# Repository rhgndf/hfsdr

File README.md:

# hfsdr

HFSDR: host software, firmware, and hardware design for the HFSDR USB device.

[Board PCB Files viewer](https://rhgndf.github.io/hfsdr/hardware)

## Getting started

Portable Mode (not connected to a PC)

1. Press the Rotary Encoder to 
    1. Enable/ Disable FM Audio Out mode (on disabled, it plays a constant tone)
    2. Cycle through different LED modes
<!--2. Turn the radio to change the FM Radio Frequency-->

Connected to a PC

1. Go to [the web ui](https://rhgndf.github.io/hfsdr/)
2. Connect & Pair a device
3. Set the frequency & gain
4. Pair the device again
5. Waterfall of the wireless world should start. If it doesn't look like [this](https://hackin7.github.io/lain-sdr-chall/assets/sample-C2LA0HHR.png), unplug the device and try again

- **User manual (slides):** [HFSDR User Manual](https://docs.google.com/presentation/d/1T5zb-2KSN37Saw5E9nwcajVOSR3CzVYfAOpIypQLBcQ/edit?usp=sharing)
- **Lain Themed Web UI** [lain-sdr-ui](https://hackin7.github.io/lain-sdr-chall)
- **Host testing (Python probe, GNU Radio `.grc` examples, drivers, protocol):** [docs/host-guide.md](docs/host-guide.md)

## Troubleshooting

- **No firmware:** Enter the bootloader by holding down BOOT and pressing the RST button. Use `wchisp` to flash the elf file in the releases
- **USB / stream flaky:** Unplug the board or reset it a few times. The host stack sometimes needs a power cycle before enumeration, WinUSB binding, or streaming stabilizes.
- **Using with GNURadio/ Python Scripting:** See the driver and probe sections in [docs/host-guide.md](docs/host-guide.md).
- **Reset:** Do not hold the reset button for too long 

## Repository layout

| Path | Contents |
|------|----------|
| `ch32v305/` | Firmware (CH32V305). Build, flash, toolchain: [ch32v305/README.md](ch32v305/README.md). |
| `client-sw/` | Host Python (`hfsdr_probe`, PyUSB helpers), GNU Radio blocks and examples (`gr-hfsdr-lib`, `.grc`). |
| `docs/` | [host-guide.md](docs/host-guide.md) — primary host-side documentation. |
| `hardware/` | KiCad project and related hardware files. |
| `scripts/` | Helper scripts (e.g. udev `99-hfsdr.rules`, Windows USB checks). |
| `ui/` | WebUSB Web UI (Svelte/Vite). Deployed build: `homepage` in [ui/package.json](ui/package.json). |

## Credits

1. rhgndf - hard carry schematic & everything inside actually
2. Hackin7 - Art, PCB rough layout & routing & some embedded
3. Hack & Roll Cursor Credits + Codex - allow us to do this while being overseas/ having full time jobs
4. https://github.com/ttrftech/CentSDR - Useful reference

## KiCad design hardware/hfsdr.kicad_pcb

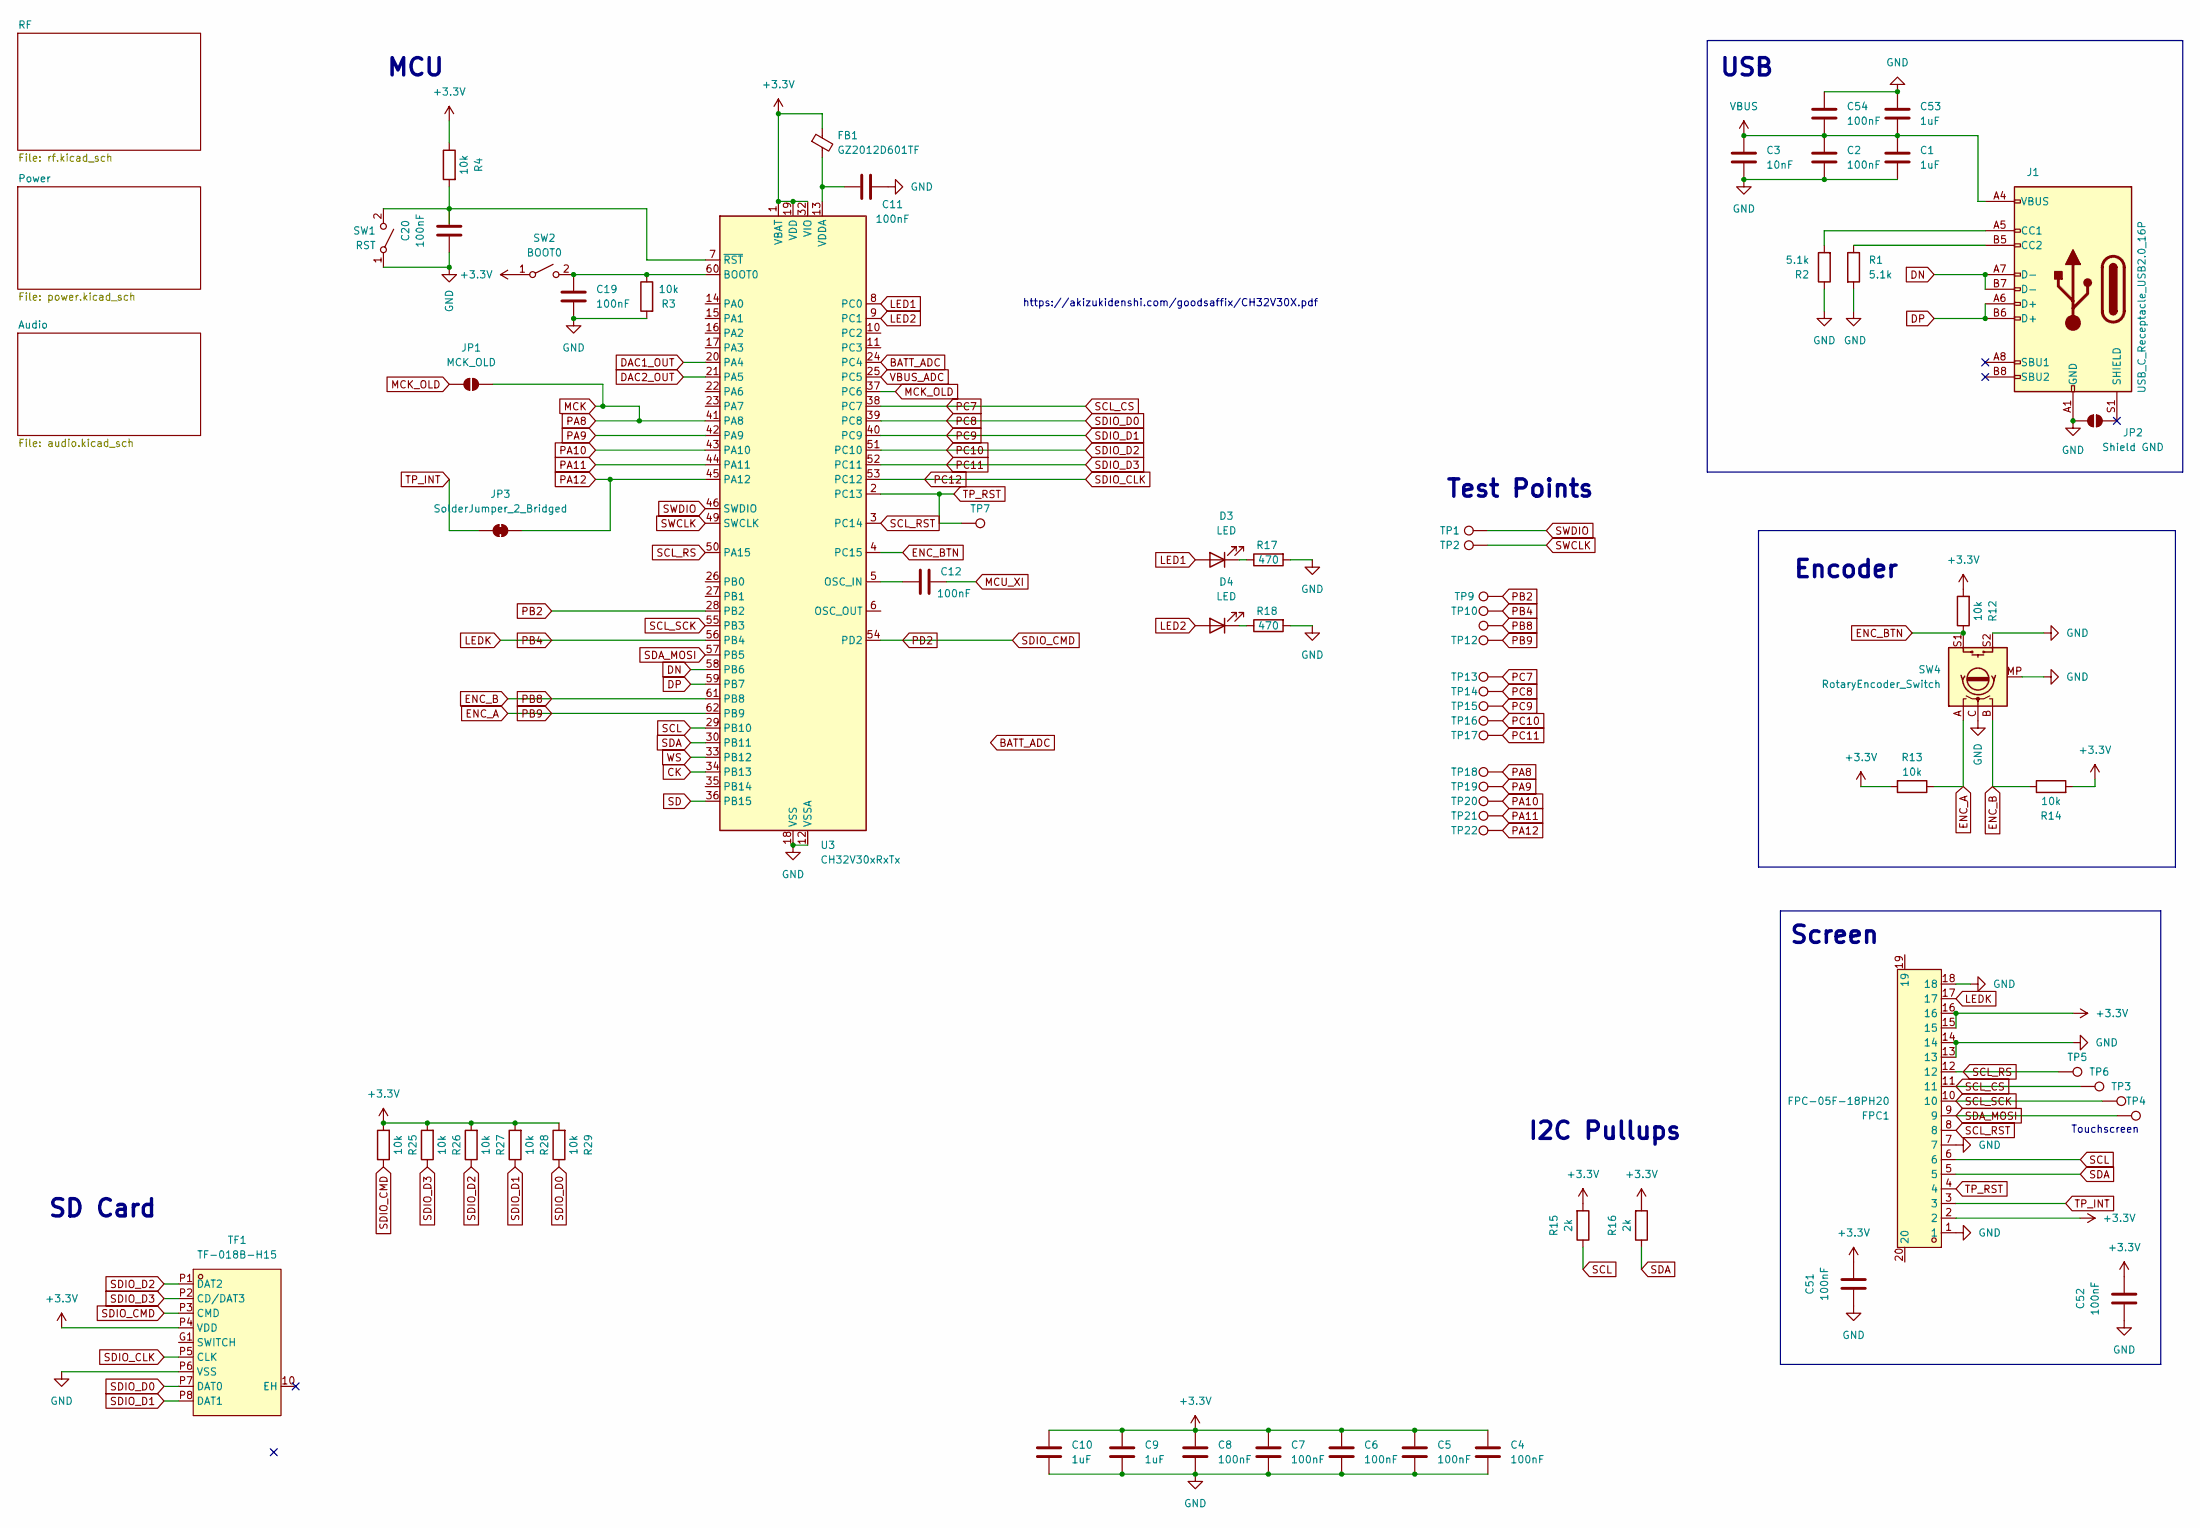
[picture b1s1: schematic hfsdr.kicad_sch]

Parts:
C1, C9, C10, C53: 1uF; C_0805_2012Metric_Pad1.18x1.45mm_HandSolder
C2, C4, C5, C6, C7, C8, C11, C12, C19, C20, C51, C52, C54: 100nF; C_0805_2012Metric_Pad1.18x1.45mm_HandSolder
C3: 10nF; C_0805_2012Metric_Pad1.18x1.45mm_HandSolder
D3, D4: LED; LED1206-RD_RED_XL-3216SURC-FB
FB1: GZ2012D601TF; L_0805_2012Metric_Pad1.05x1.20mm_HandSolder
FPC1: FPC-05F-18PH20; FPC-SMD_18P-P0.50_FPC-05F-18PH20; LCSC Part C2856802
J1: USB_C_Receptacle_USB2.0_16P; USB_C_Receptacle_GCT_USB4105-xx-A_16P_TopMnt_Horizontal
JP1: MCK_OLD; SolderJumper-2_P1.3mm_Open_RoundedPad1.0x1.5mm
JP2: Shield GND; SolderJumper-2_P1.3mm_Open_RoundedPad1.0x1.5mm
JP3: SolderJumper_2_Bridged; SolderJumper-2_P1.3mm_Bridged2Bar_RoundedPad1.0x1.5mm
R1, R2: 5.1k; R_0805_2012Metric_Pad1.20x1.40mm_HandSolder
R3, R4, R12, R13, R14, R25, R26, R27, R28, R29: 10k; R_0805_2012Metric_Pad1.20x1.40mm_HandSolder
R15, R16: 2k; R_0805_2012Metric_Pad1.20x1.40mm_HandSolder
R17, R18: 470; R_0805_2012Metric
SW1: RST; SW_Push_1P1T_XKB_TS-1187A
SW2: BOOT0; SW_Push_1P1T_XKB_TS-1187A
SW4: RotaryEncoder_Switch; RotaryEncoder_Alps_EC11E-Switch_Vertical_H20mm_MountingHoles
TF1: TF-018B-H15; TF-SMD_TF-018B-H15; LCSC Part C2962372
TP1, TP2, TP3, TP4, TP5, TP6, TP7, TP9, TP10, TP11, TP12, TP13, TP14, TP15, TP16, TP17, TP18, TP19, TP20, TP21, TP22: TestPoint; TestPoint_Pad_1.0x1.0mm
U3: CH32V30xRxTx; LQFP-64_10x10mm_P0.5mm

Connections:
+3.3V: C4.1, C5.1, C6.1, C7.1, C8.1, C9.1, C10.1, C51.2, C52.2, FB1.1, FPC1.2, FPC1.15, FPC1.16, R4.1, R12.2, R13.2, R14.2, R15.2, R16.2, R25.2, R26.2, R27.2, R28.2, R29.2, SW2.1 (A), TF1.P4 (VDD), U3.1 (VBAT), U3.19 (VDD), U3.32 (VIO), U3.48 (VDD), U3.64 (VIO); also elsewhere on the board
BATT_ADC: U3.24 (PC4); also elsewhere on the board
CK: U3.34 (PB13); also elsewhere on the board
DAC1_OUT: U3.20 (PA4); also elsewhere on the board
DAC2_OUT: U3.21 (PA5); also elsewhere on the board
DN: J1.A7 (D-), J1.B7 (D-), U3.58 (PB6)
DP: J1.A6 (D+), J1.B6 (D+), U3.59 (PB7)
ENC_A: R13.1, SW4.A, TP12.1 (1_1), U3.62 (PB9)
ENC_B: R14.1, SW4.B, TP11.1 (1_1), U3.61 (PB8)
ENC_BTN: R12.1, SW4.S1, U3.4 (PC15)
GND: C1.2, C2.2, C3.2, C4.2, C5.2, C6.2, C7.2, C8.2, C9.2, C10.2, C11.2, C19.2, C20.1, C51.1, C52.1, C53.1, C54.1, FPC1.1, FPC1.7, FPC1.13, FPC1.14, FPC1.18, J1.A1 (GND), J1.A12 (GND), J1.B1 (GND), J1.B12 (GND), JP2.1 (A_1), R1.2, R2.1, R3.2, R17.2, R18.2, SW1.1 (A), SW4.C, SW4.MP, SW4.S2, TF1.P6 (VSS), U3.12 (VSSA), U3.18 (VSS), U3.31 (VSS), U3.47 (VSS), U3.63 (VSS); also elsewhere on the board
LED1: D3.2 (A), U3.8 (PC0)
LED2: D4.2 (A), U3.9 (PC1)
LEDK: FPC1.17, TP10.1 (1_1), U3.56 (PB4)
MCK: JP1.2 (B), TP18.1 (1_1), U3.41 (PA8); also elsewhere on the board
MCK_OLD: JP1.1 (A), U3.37 (PC6)
MCU_XI: C12.2; also elsewhere on the board
unnamed: D3.1 (K), R17.1
unnamed: D4.1 (K), R18.1
unnamed: J1.A5 (CC1), R2.2
unnamed: J1.B5 (CC2), R1.1
unnamed: C20.2, R4.2, SW1.2 (B), U3.7 (~RST)
unnamed: C19.1, R3.1, SW2.2 (B), U3.60 (BOOT0)
unnamed: C12.1, U3.5 (OSC_IN)
unnamed: C11.1, FB1.2, U3.13 (VDDA)
PA9: TP19.1 (1_1), U3.42 (PA9)
PA10: TP20.1 (1_1), U3.43 (PA10)
PA11: TP21.1 (1_1), U3.44 (PA11); also elsewhere on the board
PA12: JP3.2 (B), TP22.1 (1_1), U3.45 (PA12)
PB2: TP9.1 (1_1), U3.28 (PB2)
PC7: FPC1.11, TP6.1 (1_1), TP13.1 (1_1), U3.38 (PC7)
PC8: R29.1, TF1.P7 (DAT0), TP14.1 (1_1), U3.39 (PC8)
PC9: R28.1, TF1.P8 (DAT1), TP15.1 (1_1), U3.40 (PC9)
PC10: R27.1, TF1.P1 (DAT2), TP16.1 (1_1), U3.51 (PC10)
PC11: R26.1, TF1.P2 (CD/DAT3), TP17.1 (1_1), U3.52 (PC11)
PC12: TF1.P5 (CLK), U3.53 (PC12)
PD2: R25.1, TF1.P3 (CMD), U3.54 (PD2)
SCL: FPC1.6, R15.1, U3.29 (PB10); also elsewhere on the board
SCL_RS: FPC1.12, TP5.1 (1_1), U3.50 (PA15)
SCL_RST: FPC1.8, U3.3 (PC14)
SCL_SCK: FPC1.10, TP3.1 (1_1), U3.55 (PB3)
SD: U3.36 (PB15); also elsewhere on the board
SDA: FPC1.5, R16.1, U3.30 (PB11); also elsewhere on the board
SDA_MOSI: FPC1.9, TP4.1 (1_1), U3.57 (PB5)
SWCLK: TP2.1 (1_1), U3.49 (SWCLK)
SWDIO: TP1.1 (1_1), U3.46 (SWDIO)
TP_INT: FPC1.3, JP3.1 (A)
TP_RST: FPC1.4, TP7.1 (1_1), U3.2 (PC13)
VBUS: C1.1, C2.1, C3.1, C53.2, C54.2, J1.A4 (VBUS), J1.A9 (VBUS), J1.B4 (VBUS), J1.B9 (VBUS); also elsewhere on the board
VBUS_ADC: U3.25 (PC5); also elsewhere on the board
WS: U3.33 (PB12); also elsewhere on the board

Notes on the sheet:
USB
SD Card
https://akizukidenshi.com/goodsaffix/CH32V30X.pdf
Encoder
Touchscreen
Screen
MCU
Test Points
I2C Pullups

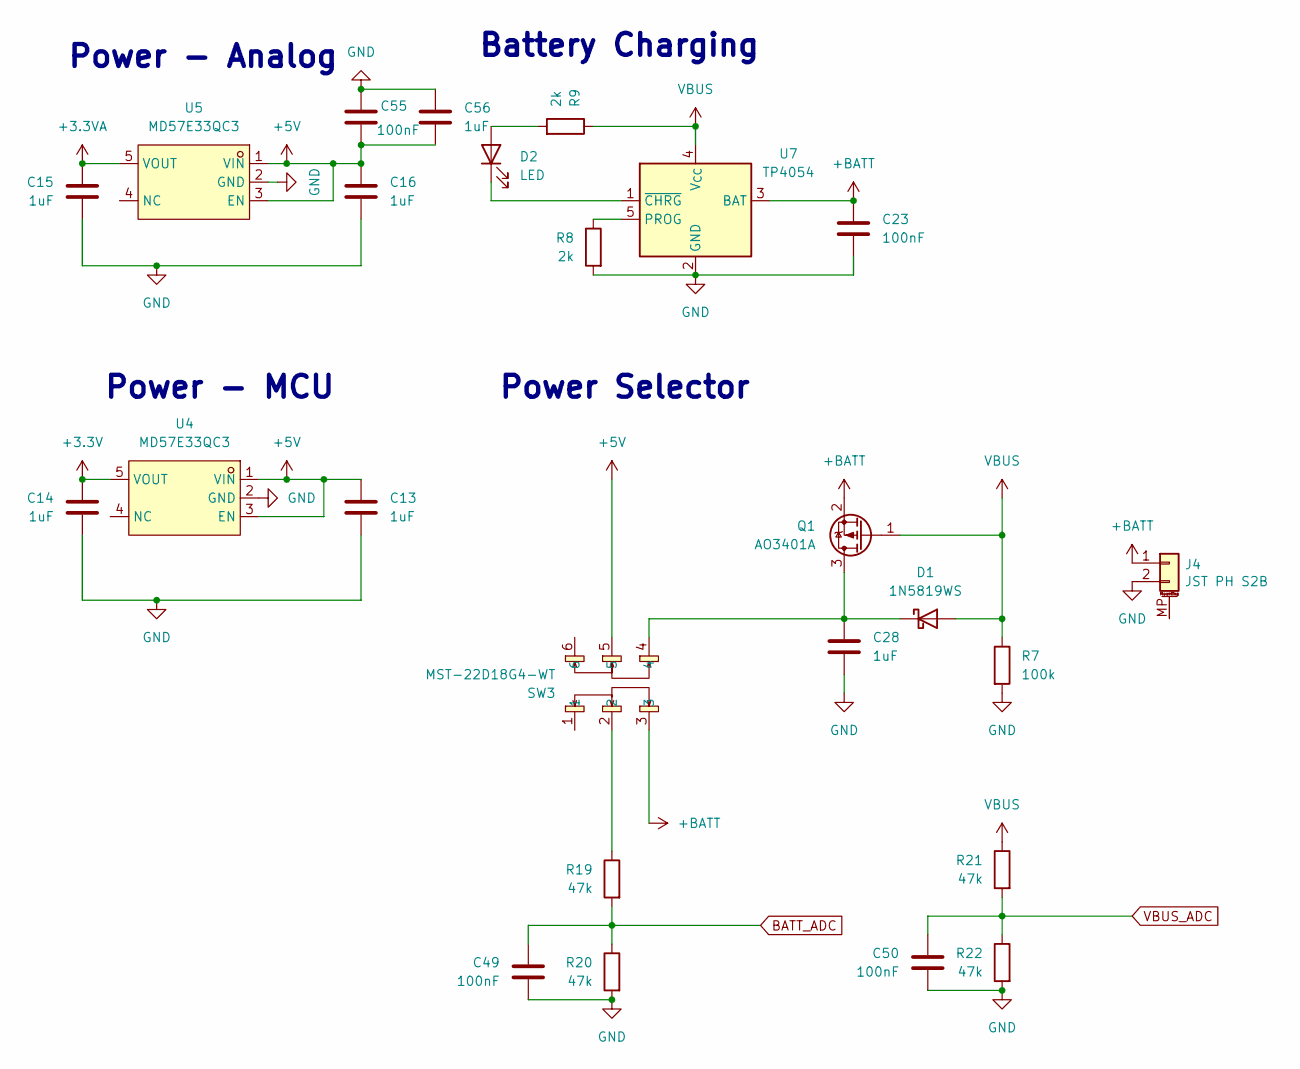
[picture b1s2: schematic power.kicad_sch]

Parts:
C13, C14, C15, C16, C28, C56: 1uF; C_0805_2012Metric_Pad1.18x1.45mm_HandSolder
C23, C49, C50, C55: 100nF; C_0805_2012Metric_Pad1.18x1.45mm_HandSolder
D1: 1N5819WS; D_SOD-323
D2: LED; LED_0805_2012Metric
J4: JST PH S2B; JST_PH_S2B-PH-SM4-TB_1x02-1MP_P2.00mm_Horizontal; LCSC C505023
Q1: AO3401A; SOT-23
R7: 100k; R_0805_2012Metric_Pad1.20x1.40mm_HandSolder
R8, R9: 2k; R_0805_2012Metric_Pad1.20x1.40mm_HandSolder
R19, R20, R21, R22: 47k; R_0805_2012Metric_Pad1.20x1.40mm_HandSolder
SW3: MST-22D18G4-WT; SW-SMD_MST-22D18G4-WT; LCSC Part C7507448
U4, U5: MD57E33QC3; SOT-23-5_L3.0-W1.7-P0.95-LS2.8-BR; LCSC Part C920562
U7: TP4054; TSOT-23-5

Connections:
+3.3V: C14.1, U4.5 (VOUT); also elsewhere on the board
+3.3VA: C15.1, U5.5 (VOUT); also elsewhere on the board
+5V: C13.1, C16.1, C55.2, C56.2, SW3.5, U4.1 (VIN), U4.3 (EN), U5.1 (VIN), U5.3 (EN)
+BATT: C23.1, J4.1, Q1.2 (S), SW3.3, U7.3 (BAT)
BATT_ADC: C49.1, R19.2, R20.1; also elsewhere on the board
GND: C13.2, C14.2, C15.2, C16.2, C23.2, C28.2, C49.2, C50.2, C55.1, C56.1, J4.2, R7.2, R8.2, R20.2, R22.2, U4.2 (GND), U5.2 (GND), U7.2 (GND); also elsewhere on the board
unnamed: C28.1, D1.1 (K), Q1.3 (D), SW3.4
unnamed: D2.2 (A), R9.2
unnamed: D2.1 (K), U7.1 (~CHRG)
unnamed: R19.1, SW3.2
unnamed: R8.1, U7.5 (PROG)
VBUS: D1.2 (A), Q1.1 (G), R7.1, R9.1, R21.1, U7.4 (V_{CC}); also elsewhere on the board
VBUS_ADC: C50.1, R21.2, R22.1; also elsewhere on the board

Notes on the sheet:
Power - Analog
Battery Charging
Power - MCU
Power Selector

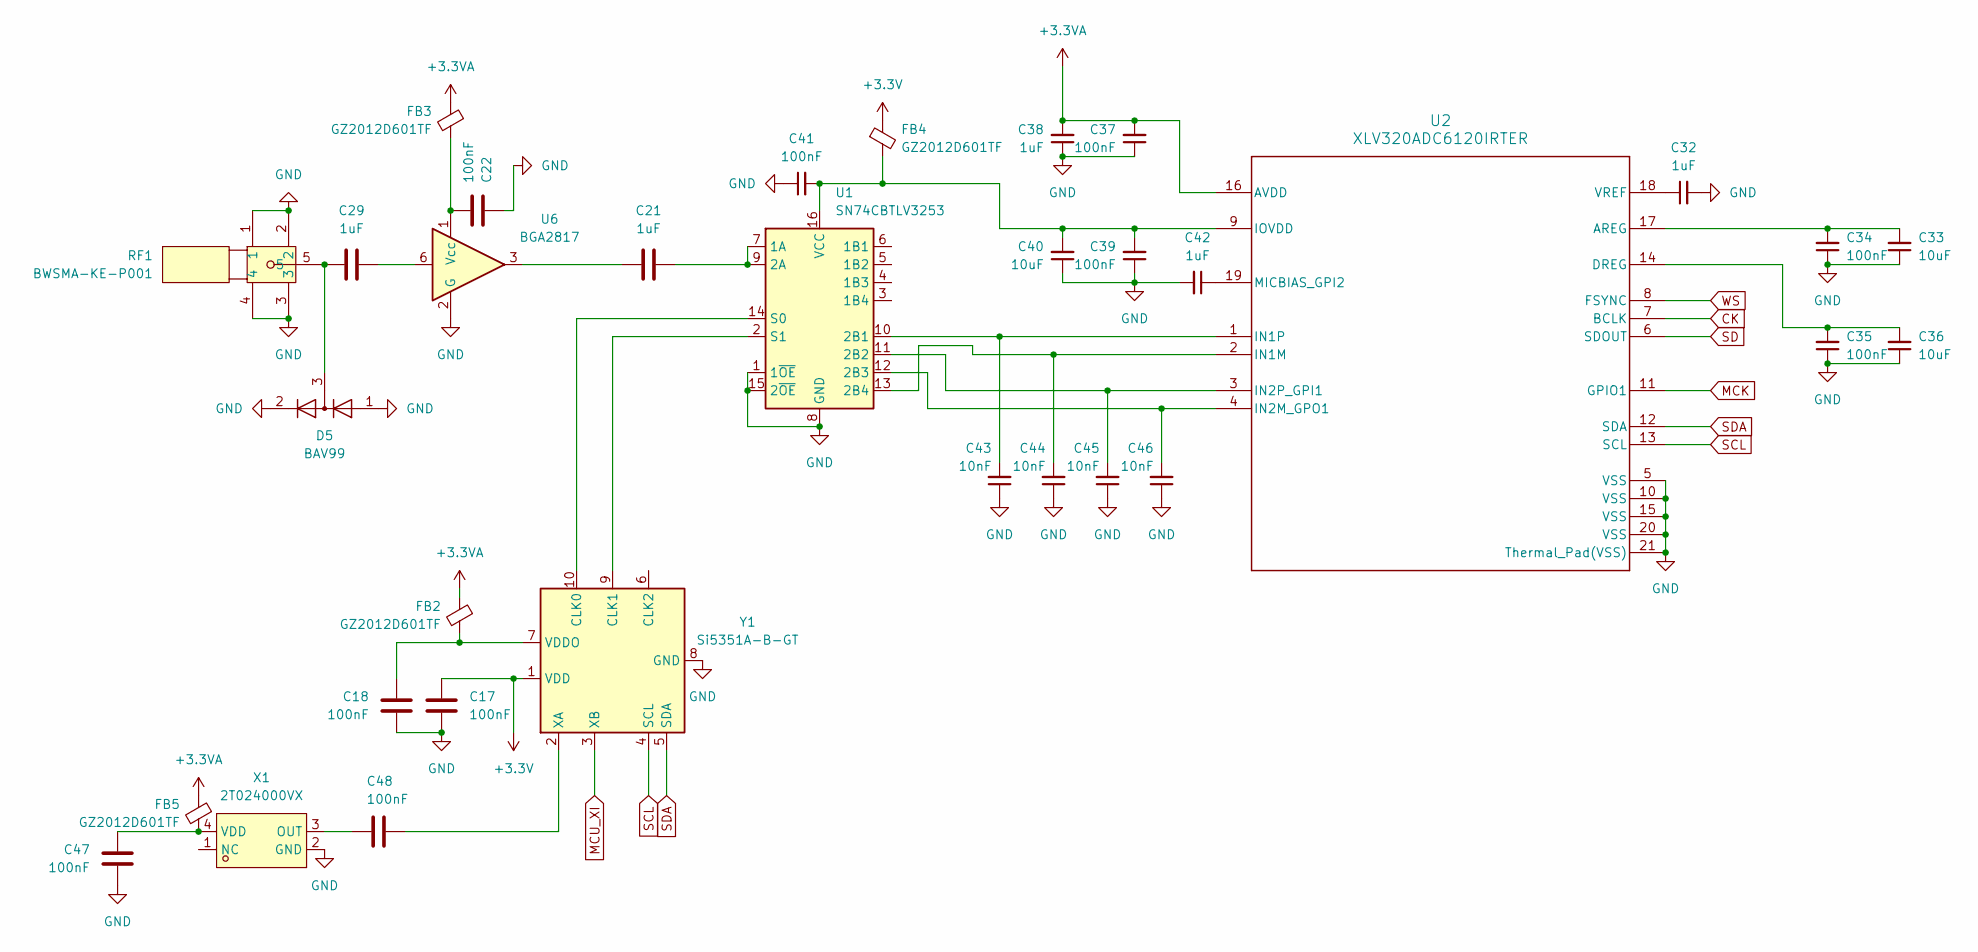
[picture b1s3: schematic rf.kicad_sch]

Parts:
C17, C18, C22, C34, C35, C37, C39, C41, C47, C48: 100nF; C_0805_2012Metric_Pad1.18x1.45mm_HandSolder
C21, C29, C32, C38, C42: 1uF; C_0805_2012Metric_Pad1.18x1.45mm_HandSolder
C33, C36, C40: 10uF; C_0805_2012Metric_Pad1.18x1.45mm_HandSolder
C43, C44, C45, C46: 10nF; C_0805_2012Metric_Pad1.18x1.45mm_HandSolder
D5: BAV99; SOT-23
FB2, FB3, FB4, FB5: GZ2012D601TF; L_0805_2012Metric_Pad1.05x1.20mm_HandSolder
RF1: BWSMA-KE-P001; SMA-SMD_BWSMA-KE-P001; LCSC Part C496550
U1: SN74CBTLV3253; SOIC-16_3.9x9.9mm_P1.27mm
U2: XLV320ADC6120IRTER; RTE0020A-MFG
U6: BGA2817; SOT-363_SC-70-6
X1: 2T024000VX; OSC-SMD_4P-L2.5-W2.0-BL_X1G0054210307; LCSC Part C47018486
Y1: Si5351A-B-GT; MSOP-10_3x3mm_P0.5mm

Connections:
+3.3V: C17.2, FB4.1, Y1.1 (VDD); also elsewhere on the board
+3.3VA: C37.2, C38.2, FB2.1, FB3.1, FB5.1, U2.16 (AVDD); also elsewhere on the board
CK: U2.7 (BCLK); also elsewhere on the board
GND: C17.1, C18.2, C22.1, C32.2, C33.1, C34.1, C35.1, C36.1, C37.1, C38.1, C39.1, C40.1, C41.1, C42.2, C43.1, C44.1, C45.1, C46.1, C47.2, D5.1 (K), D5.2 (A), RF1.1, RF1.2, RF1.3, RF1.4, U1.1 (1~OE), U1.8 (GND), U1.15 (2~OE), U2.5 (VSS), U2.10 (VSS), U2.15 (VSS), U2.20 (VSS), U2.21 (Thermal_Pad(VSS)), U6.2 (G), U6.4 (G), U6.5 (G), X1.2 (GND), Y1.8 (GND); also elsewhere on the board
MCK: U2.11 (GPIO1); also elsewhere on the board
MCU_XI: Y1.3 (XB); also elsewhere on the board
unnamed: C21.2, U6.3
unnamed: C29.1, U6.6
unnamed: C29.2, D5.3 (K), RF1.5
unnamed: C21.1, U1.7 (1A), U1.9 (2A)
unnamed: C43.2, U1.10 (2B1), U2.1 (IN1P)
unnamed: C45.2, U1.11 (2B2), U2.3 (IN2P_GPI1)
unnamed: C46.2, U1.12 (2B3), U2.4 (IN2M_GPO1)
unnamed: C44.2, U1.13 (2B4), U2.2 (IN1M)
unnamed: U1.14 (S0), Y1.10 (CLK0)
unnamed: U1.2 (S1), Y1.9 (CLK1)
unnamed: C39.2, C40.2, C41.2, FB4.2, U1.16 (VCC), U2.9 (IOVDD)
unnamed: C33.2, C34.2, U2.17 (AREG)
unnamed: C35.2, C36.2, U2.14 (DREG)
unnamed: C42.1, U2.19 (MICBIAS_GPI2)
unnamed: C32.1, U2.18 (VREF)
unnamed: C22.2, FB3.2, U6.1 (Vcc)
unnamed: C48.2, X1.3 (OUT)
unnamed: C47.1, FB5.2, X1.4 (VDD)
unnamed: C18.1, FB2.2, Y1.7 (VDDO)
unnamed: C48.1, Y1.2 (XA)
SCL: U2.13 (SCL), Y1.4 (SCL); also elsewhere on the board
SD: U2.6 (SDOUT); also elsewhere on the board
SDA: U2.12 (SDA), Y1.5 (SDA); also elsewhere on the board
WS: U2.8 (FSYNC); also elsewhere on the board

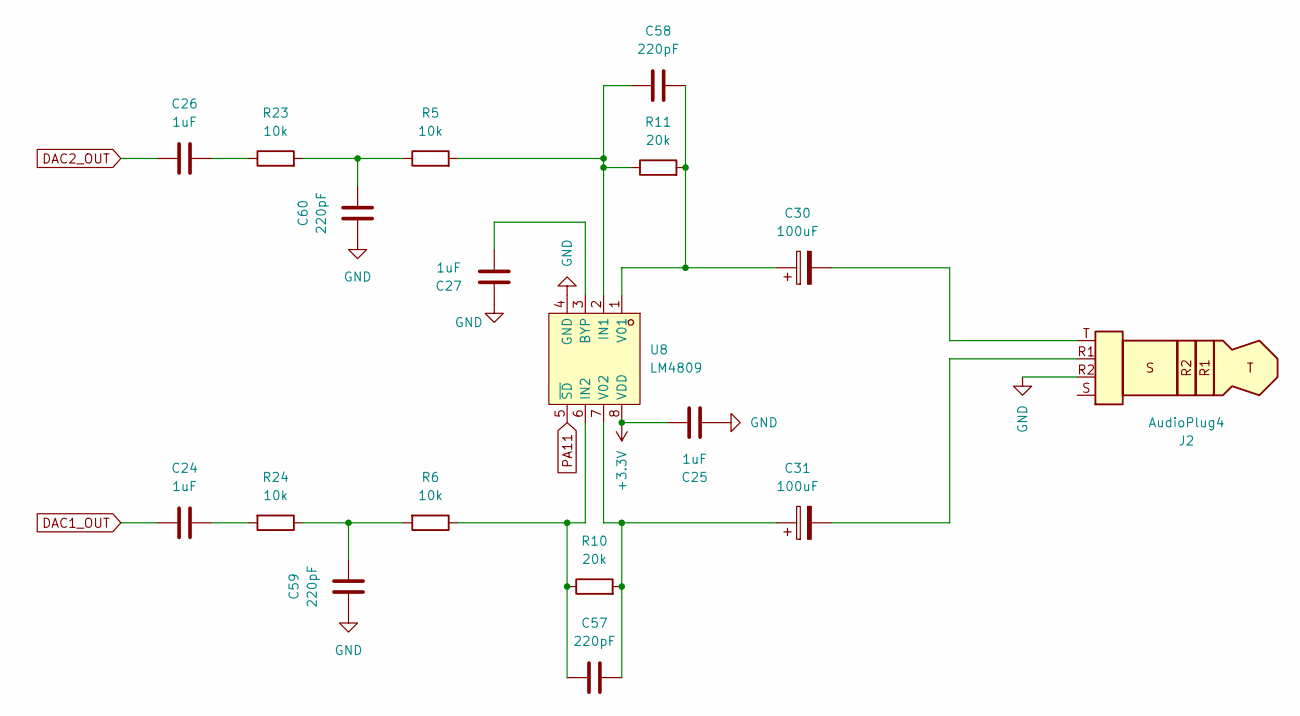
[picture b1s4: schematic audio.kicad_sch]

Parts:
C24, C25, C26, C27: 1uF; C_0805_2012Metric_Pad1.18x1.45mm_HandSolder
C30, C31: 100uF; CP_EIA-3528-15_AVX-H_HandSolder
C57, C58, C59, C60: 220pF; C_0805_2012Metric_Pad1.18x1.45mm_HandSolder
J2: AudioPlug4; Jack_3.5mm_KoreanHropartsElec_PJ-320D-4A_Horizontal
R5, R6, R23, R24: 10k; R_0805_2012Metric_Pad1.20x1.40mm_HandSolder
R10, R11: 20k; R_0805_2012Metric_Pad1.20x1.40mm_HandSolder
U8: LM4809; MSOP-8_L3.0-W3.0-P0.65-LS4.9-BL; LCSC Part C5125075

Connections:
+3.3V: C25.2, U8.8 (VDD); also elsewhere on the board
DAC1_OUT: C24.2; also elsewhere on the board
DAC2_OUT: C26.2; also elsewhere on the board
GND: C25.1, C27.2, C59.2, C60.2, J2.R2, U8.4 (GND); also elsewhere on the board
unnamed: C24.1, R24.2
unnamed: C26.1, R23.1
unnamed: C30.2, J2.T
unnamed: C31.2, J2.R1
unnamed: C59.1, R6.2, R24.1
unnamed: C60.1, R5.1, R23.2
unnamed: C27.1, U8.3 (BYP)
unnamed: C58.2, R5.2, R11.1, U8.2 (IN1)
unnamed: C57.2, R6.1, R10.1, U8.6 (IN2)
unnamed: C30.1, C58.1, R11.2, U8.1 (V01)
unnamed: C31.1, C57.1, R10.2, U8.7 (V02)
PA11: U8.5 (~SD); also elsewhere on the board

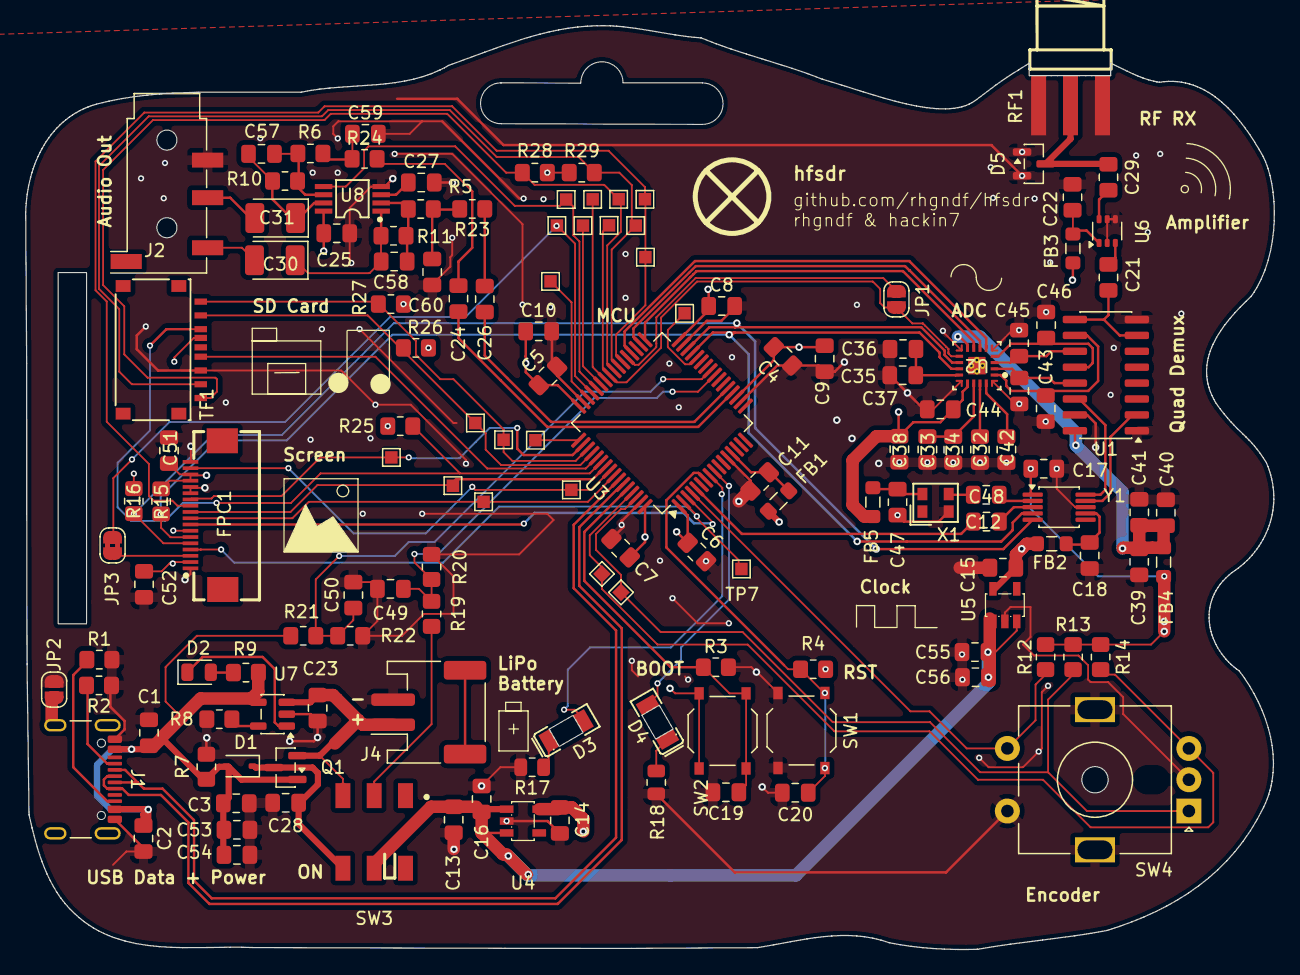
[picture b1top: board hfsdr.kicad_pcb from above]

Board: 4 copper layers, 99.8 x 73.8 mm, 144 parts (0 on the bottom side), 90 nets.

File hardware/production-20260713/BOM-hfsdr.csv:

Comment,Designator,Footprint,LCSC,Quantity
100k,R7,R_0805_2012Metric_Pad1.20x1.40mm_HandSolder,C149504,1
100nF,"C11,C12,C17,C18,C19,C2,C20,C22,C23,C34,C35,C37,C39,C4,C41,C47,C48,C49,C5,C50,C51,C52,C54,C55,C6,C7,C8",C_0805_2012Metric_Pad1.18x1.45mm_HandSolder,C49678,27
100uF,"C30,C31",CP_EIA-3528-15_AVX-H_HandSolder,C16133,2
10k,"R12,R13,R14,R23,R24,R25,R26,R27,R28,R29,R3,R4,R5,R6",R_0805_2012Metric_Pad1.20x1.40mm_HandSolder,C17414,14
10nF,"C3,C43,C44,C45,C46",C_0805_2012Metric_Pad1.18x1.45mm_HandSolder,C97905,5
10uF,"C33,C36,C40",C_0805_2012Metric_Pad1.18x1.45mm_HandSolder,C15850,3
1N5819WS,D1,D_SOD-323,C191023,1
1uF,"C1,C10,C13,C14,C15,C16,C21,C24,C25,C26,C27,C28,C29,C32,C38,C42,C53,C56,C9",C_0805_2012Metric_Pad1.18x1.45mm_HandSolder,C28323,19
20k,"R10,R11",R_0805_2012Metric_Pad1.20x1.40mm_HandSolder,C4328,2
220pF,"C57,C58,C59,C60",C_0805_2012Metric_Pad1.18x1.45mm_HandSolder,C1790,4
2T024000VX,X1,OSC-SMD_4P-L2.5-W2.0-BL_X1G0054210307,C47018486,1
2k,"R15,R16,R8,R9",R_0805_2012Metric_Pad1.20x1.40mm_HandSolder,C17604,4
470,"R17,R18",R_0805_2012Metric,C17710,2
47k,"R19,R20,R21,R22",R_0805_2012Metric_Pad1.20x1.40mm_HandSolder,C17713,4
5.1k,"R1,R2",R_0805_2012Metric_Pad1.20x1.40mm_HandSolder,C27834,2
AO3401A,Q1,SOT-23,C15127,1
AudioPlug4,J2,Jack_3.5mm_KoreanHropartsElec_PJ-320D-4A_Horizontal,C95562,1
BAV99,D5,SOT-23,C7420336,1
BGA2817,U6,SOT-363_SC-70-6,C2654187,1
BOOT0,SW2,SW_Push_1P1T_XKB_TS-1187A,C318884,1
BWSMA-KE-P001,RF1,SMA-SMD_BWSMA-KE-P001,C496550,1
CH32V30xRxTx,U3,LQFP-64_10x10mm_P0.5mm,C5187529,1
FPC-05F-18PH20,FPC1,FPC-SMD_18P-P0.50_FPC-05F-18PH20,C2856802,1
GZ2012D601TF,"FB1,FB2,FB3,FB4,FB5",L_0805_2012Metric_Pad1.05x1.20mm_HandSolder,C1017,5
JST PH S2B,J4,JST_PH_S2B-PH-SM4-TB_1x02-1MP_P2.00mm_Horizontal,C7433648,1
LED,D2,LED_0805_2012Metric,C2297,1
LED,"D3,D4",LED1206-RD_RED_XL-3216SURC-FB,C3646941,2
LM4809,U8,MSOP-8_L3.0-W3.0-P0.65-LS4.9-BL,C5125075,1
MD57E33QC3,"U4,U5",SOT-23-5_L3.0-W1.7-P0.95-LS2.8-BR,C920562,2
MST-22D18G4-WT,SW3,SW-SMD_MST-22D18G4-WT,C7507448,1
RST,SW1,SW_Push_1P1T_XKB_TS-1187A,C318884,1
SN74CBTLV3253,U1,SOIC-16_3.9x9.9mm_P1.27mm,C543079,1
Si5351A-B-GT,Y1,MSOP-10_3x3mm_P0.5mm,C1509083,1
TF-018B-H15,TF1,TF-SMD_TF-018B-H15,C2962372,1
TP4054,U7,TSOT-23-5,C32574,1
USB_C_Receptacle_USB2.0_16P,J1,USB_C_Receptacle_GCT_USB4105-xx-A_16P_TopMnt_Horizontal,C2765186,1
XLV320ADC6120IRTER,U2,RTE0020A-MFG,C2874822,1
RotaryEncoder_Switch,SW4,RotaryEncoder_Alps_EC11E-Switch_Vertical_H20mm_MountingHoles,,1
TestPoint,TP20,TestPoint_Pad_1.0x1.0mm,,1
TestPoint,TP16,TestPoint_Pad_1.0x1.0mm,,1
TestPoint,TP12,TestPoint_Pad_1.0x1.0mm,,1
TestPoint,TP10,TestPoint_Pad_1.0x1.0mm,,1
TestPoint,TP7,TestPoint_Pad_1.0x1.0mm,,1
TestPoint,TP17,TestPoint_Pad_1.0x1.0mm,,1
TestPoint,TP4,TestPoint_Pad_1.0x1.0mm,,1
TestPoint,TP6,TestPoint_Pad_1.0x1.0mm,,1
TestPoint,TP3,TestPoint_Pad_1.0x1.0mm,,1
TestPoint,TP22,TestPoint_Pad_1.0x1.0mm,,1
TestPoint,TP9,TestPoint_Pad_1.0x1.0mm,,1
TestPoint,TP1,TestPoint_Pad_1.0x1.0mm,,1
TestPoint,TP18,TestPoint_Pad_1.0x1.0mm,,1
TestPoint,TP13,TestPoint_Pad_1.0x1.0mm,,1
TestPoint,TP11,TestPoint_Pad_1.0x1.0mm,,1
TestPoint,TP21,TestPoint_Pad_1.0x1.0mm,,1
TestPoint,TP15,TestPoint_Pad_1.0x1.0mm,,1
TestPoint,TP14,TestPoint_Pad_1.0x1.0mm,,1
TestPoint,TP5,TestPoint_Pad_1.0x1.0mm,,1
TestPoint,TP2,TestPoint_Pad_1.0x1.0mm,,1
TestPoint,TP19,TestPoint_Pad_1.0x1.0mm,,1

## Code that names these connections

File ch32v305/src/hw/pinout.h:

#ifndef PINOUT_H
#define PINOUT_H

#include "ch32v30x.h"

// --- nanoCH32V305 --------------------------------------
/* Global define */
#define LED_GPIO_PORT      GPIOA
#define LED_GPIO_PIN       GPIO_Pin_3

// --- hfsdr badge ---------------------------------------
/* LEDs */
#define LED1_GPIO_PORT     GPIOC
#define LED1_GPIO_PIN      GPIO_Pin_0
#define LED2_GPIO_PORT     GPIOC
#define LED2_GPIO_PIN      GPIO_Pin_1

/* DAC */
#define DAC1_OUT_GPIO_PORT GPIOA
#define DAC1_OUT_GPIO_PIN  GPIO_Pin_4
#define DAC2_OUT_GPIO_PORT GPIOA
#define DAC2_OUT_GPIO_PIN  GPIO_Pin_5
#define DAC_AMP_SD_GPIO_PORT GPIOA
#define DAC_AMP_SD_GPIO_PIN  GPIO_Pin_11

/* Encoder */
#define ENC_A_GPIO_PORT    GPIOB
#define ENC_A_GPIO_PIN     GPIO_Pin_8
#define ENC_B_GPIO_PORT    GPIOB
#define ENC_B_GPIO_PIN     GPIO_Pin_9
#define ENC_BTN_GPIO_PORT  GPIOC
#define ENC_BTN_GPIO_PIN   GPIO_Pin_15

/* ADC sense */
#define BATT_ADC_GPIO_PORT GPIOC
#define BATT_ADC_GPIO_PIN  GPIO_Pin_4
#define VBUS_ADC_GPIO_PORT GPIOC
#define VBUS_ADC_GPIO_PIN  GPIO_Pin_5

/* I2S - ADC */
#define I2S_WS_GPIO_PORT   GPIOB
#define I2S_WS_GPIO_PIN    GPIO_Pin_12
#define I2S_CK_GPIO_PORT   GPIOB
#define I2S_CK_GPIO_PIN    GPIO_Pin_13
#define I2S_SD_GPIO_PORT   GPIOB
#define I2S_SD_GPIO_PIN    GPIO_Pin_15
#define I2S_MCK_GPIO_PORT  GPIOC
#define I2S_MCK_GPIO_PIN   GPIO_Pin_6

/* SPI3 - Screen SCK/MOSI on PB3/PB5 */
#define SPI3_SCL_SCK_GPIO_PORT  GPIOB
#define SPI3_SCL_SCK_GPIO_PIN   GPIO_Pin_3
#define SPI3_SDA_MOSI_GPIO_PORT GPIOB
#define SPI3_SDA_MOSI_GPIO_PIN  GPIO_Pin_5

/* ST7789 + touch: command vs SPI data is RS (register select), not a separate DC pin. */
/* ST7789 reset: active-low (drive low to reset, high for normal run). */
#define ST7789_RST_GPIO_PORT  GPIOC
#define ST7789_RST_GPIO_PIN   GPIO_Pin_14
/* CST328 touch panel reset (active-low): PC13 */
#define TP_RST_GPIO_PORT      GPIOC
#define TP_RST_GPIO_PIN       GPIO_Pin_13
/* CST328 touch panel IRQ (open-drain output from chip, active-low): PA12 */
#define TP_INT_GPIO_PORT      GPIOA
#define TP_INT_GPIO_PIN       GPIO_Pin_12
/* Previous pinouts:
 * #define ST7789_CS_GPIO_PORT   GPIOD
 * #define ST7789_CS_GPIO_PIN    GPIO_Pin_2
 * #define ST7789_RS_GPIO_PORT   GPIOC
 * #define ST7789_RS_GPIO_PIN    GPIO_Pin_12
 */
#define ST7789_CS_GPIO_PORT   GPIOC
#define ST7789_CS_GPIO_PIN    GPIO_Pin_7
#define ST7789_RS_GPIO_PORT   GPIOA
#define ST7789_RS_GPIO_PIN    GPIO_Pin_15
#define ST7789_LEDK_GPIO_PORT GPIOB
#define ST7789_LEDK_GPIO_PIN  GPIO_Pin_4

/* I2C - Touchscreen, ADC (RS also drives LCD register select on the shared flex / routing) */
#define I2C_SCL_GPIO_PORT   GPIOB
#define I2C_SCL_GPIO_PIN    GPIO_Pin_10
#define I2C_SDA_GPIO_PORT   GPIOB
#define I2C_SDA_GPIO_PIN    GPIO_Pin_11

/* SDIO - SD Card */
#define SDIO_D0_GPIO_PORT   GPIOC
#define SDIO_D0_GPIO_PIN    GPIO_Pin_8
#define SDIO_D1_GPIO_PORT   GPIOC
#define SDIO_D1_GPIO_PIN    GPIO_Pin_9
#define SDIO_D2_GPIO_PORT   GPIOC
#define SDIO_D2_GPIO_PIN    GPIO_Pin_10
#define SDIO_D3_GPIO_PORT   GPIOC
#define SDIO_D3_GPIO_PIN    GPIO_Pin_11
#define SDIO_CLK_GPIO_PORT  GPIOC
#define SDIO_CLK_GPIO_PIN   GPIO_Pin_12
#define SDIO_CMD_GPIO_PORT  GPIOD
#define SDIO_CMD_GPIO_PIN   GPIO_Pin_2

#endif

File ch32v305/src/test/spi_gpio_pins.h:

#ifndef SPI_GPIO_PINS_H
#define SPI_GPIO_PINS_H

#include "ch32v30x.h"

/*
 * Manual GPIO control of SPI-related lines (PB3 SCK, PB5 MOSI, PD2 CS, PC12 RS, PC11 RST).
 * spi_gpio_pins_enable() turns SPI3 off and configures pins as push-pull outputs (MISO optional input).
 * spi_gpio_pins_restore_hw_spi() runs spi_hw_init() again for peripheral SPI.
 */

void spi_gpio_pins_enable(void);
void spi_gpio_pins_restore_hw_spi(void);

/* Drive SCK, MOSI, CS, RS, RST all high (call after spi_gpio_pins_enable()). */
void spi_gpio_pins_all_on(void);

void spi_gpio_sck_write(BitAction level);
void spi_gpio_mosi_write(BitAction level);
void spi_gpio_cs_write(BitAction level);
void spi_gpio_rs_write(BitAction level);
void spi_gpio_rst_write(BitAction level);

void spi_gpio_sck_toggle(void);
void spi_gpio_mosi_toggle(void);
void spi_gpio_cs_toggle(void);
void spi_gpio_rs_toggle(void);

#endif

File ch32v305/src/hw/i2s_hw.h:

#ifndef I2S_HW_H
#define I2S_HW_H

#include <stdbool.h>
#include <stdint.h>

#include "debug.h"

/*
 * SPI2 in I2S slave RX: stereo 32-bit Philips in 32-bit channel frames.
 * WS (PB12) and CK (PB13) are supplied by an external I2S controller.
 * SD (PB15) receives serial data from an external I2S ADC / codec.
 * PC6 is reserved for an alternate 24 MHz clock output from TIM8_CH1, so the
 * SPI2 MCK pin is intentionally left unused here.
 *
 * RX uses DMA1 Channel4 in circular mode. DMA half/full-transfer interrupts
 * increment a cumulative word counter and hand each completed half-buffer
 * chunk straight into the TinyUSB microphone FIFO.
 */

void i2s_hw_init(void);
void i2s_hw_deinit(void);
void i2s_hw_enable(FunctionalState state);
[[nodiscard]] bool i2s_needs_reset(void);
[[nodiscard]] uint32_t i2s_hw_rx_word_count(void);


#define I2S_HW_COMPLEX_SAMPLE_COUNT 512U

extern float i2s_fft_sample_arr[I2S_HW_COMPLEX_SAMPLE_COUNT * 2];
void i2s_fft_sample_arr_reset(void);
bool i2s_fft_sample_arr_ready(void);

#endif

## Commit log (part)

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2025-06-21 Add schematic
2025-11-29 Firmware
2025-11-29 Update schematic
2025-11-29 amp and audio
2025-12-06 arrange pcb
2025-12-07 battery switching
2025-12-16 initial component layout
2025-12-16 initial screen
2026-02-09 feat: add rough art
2026-02-09 layout + some routing
2026-02-10 feat: routing
2026-02-14 feat: outline
2026-02-14 feat: finally got art in
2026-02-14 feat: component adjustment position
2026-02-14 feat: rough routing and features
2026-02-14 feat: most rules fixed?
2026-02-14 feat: credits
2026-02-14 feat: update jlcpcb bom - not complete
2026-02-14 feat: hfsdr rough
2026-02-14 fix: minor unconnected pads
2026-02-26 feat: add pads + fix adc chip footprint
2026-02-26 feat: add front LEDs
2026-02-26 other: active layer
2026-02-27 Fix compilation
2026-02-27 Fix components
2026-02-27 feat: resize board
2026-02-27 Production ready
2026-03-05 feat: usb send test
2026-03-05 feat: usb echo example
2026-03-05 chore: refactor out usb hw
2026-03-05 feat: cursor generated code for i2c i2s and spi
2026-03-05 fix: lmao I chatgpted systick fixes - blink + usb at the same time
2026-03-05 feat: finally printing stuff
2026-03-07 Change usb write to CDC
2026-03-07 Fix warnings
2026-03-07 Add streamer firmware
2026-03-07 Update hardware
2026-03-07 Add C++ support to firmware
2026-03-07 Update tinyusb
2026-03-07 Print memory usage and README
2026-03-10 screen docs
2026-03-27 feat: usb enumeration works
    just need change from hse to hsi, because this board no clock
2026-03-28 feat: use hse 24mhz
2026-03-28 Make write print to usb serial
2026-03-28 Change to printf
2026-03-28 Change to syscalls
2026-03-29 feat: st7789 spi
2026-03-29 st7789 not working
2026-03-29 feat: square wave audio works
2026-03-29 feat: dual channel audio works
2026-03-29 feat: sine wave audio works
2026-03-30 feat: GPIO pinout test
2026-03-30 feat: ok SPI is working, or maybe it was already working
2026-03-30 feat: last spi code, i think it'll work, just hardware issue
2026-03-30 feat: blinky led lights
2026-03-30 feat: vibed the si5351
2026-03-30 feat: 320khz oscillations on si5351 hmm
2026-03-30 feat: vibed ADC
2026-03-30 static noise fake lmao
2026-03-31 feat: not working tlv stero
2026-03-31 messy code
2026-03-31 Fractional synth
2026-03-31 90 degrees phase shift clk1
2026-03-31 4MHz is still probable by the oscilloscopes
2026-03-31 feat: current tx test setup
2026-03-31 feat: i2s DMA
2026-03-31 feat: adc spam
2026-03-31 feat: rough adc plot
2026-03-31 feat: display
2026-04-01 I2S slave+DMA
2026-04-01 TLV correct biasing + 24 bit
2026-04-01 grc audio flowgraph
2026-04-01 DAC DMA
2026-04-01 i2s to USB
2026-04-01 Remove 8MHz HSE path
2026-04-02 fix usb enum
2026-04-02 webusb set frequency command
2026-04-02 hardware fix: MCO MCK + MS5351 VDD
2026-04-02 disallow other sample rates
2026-04-02 cpp test
2026-04-02 watchdog
2026-04-02 svelte+tailwind+vite
2026-04-02 add frequency setting button
2026-04-03 feat: pcb edits
2026-04-04 Fix 3d shapes
2026-04-04 hardware: rotary encoder to TIM10
2026-04-04 hardware: LEDK to TIM3
2026-04-04 feat: gnuradio windows usb device name config
2026-04-04 Audio stream to vendor endpoint + web streamer benchmark
2026-04-04 384khz + ui spectrogram
2026-04-04 Gain changes in the UI
2026-04-04 pll lock state
2026-04-04 back to 192khz
2026-04-04 Fix permission issue on windows
2026-04-04 feat: fm audio
2026-04-04 fix dropped words by sending 8 transfers at one time + tooltip
2026-04-04 pll lock display polling
2026-04-04 pll poll lock causes drops
2026-04-04 384khz
2026-04-04 Golden code
2026-04-04 hardware feat: interrupt for screen
2026-04-05 Drain I2S buffer before DMA start
2026-04-05 Fix si5351 calculation
2026-04-05 Possible fix
2026-04-05 This definitely works, verified the stream looks ok
2026-04-05 feat: added tf slot, but need to reroute some screen pins
2026-04-05 feat: tf card slot and screen rerouting
2026-04-05 feat: added silkscreen labels
2026-04-05 Ready for production
2026-04-06 fixes
2026-04-07 Protection diode
2026-04-07 si5351 fix
2026-04-07 production
2026-04-07 unsaved stuff
2026-04-15 bitslip detection initial
2026-04-22 feat: basic LED blinky modes - Press encoder button to switch LED modes
2026-04-22 feat: nicer LED blinky modes - press encoder
2026-04-22 feat: led blinky modes with morse code pattern
2026-04-23 feat: basic python connection to hfsdr
2026-04-23 feat: refactoring basic gnuradio functionality
2026-04-23 feat: combined gnuradio example
2026-04-23 feat: basic working GNURadio
2026-04-23 feat: downscaling gnuradio
2026-04-23 feat: cursor c prototype
2026-04-23 feat: functioning fm demod I think?
2026-04-23 feat: encoder toggle
2026-04-23 feat: change no fm output mode to constant tone
2026-04-23 feat: gh pages deployment
2026-04-23 chore: used cursor to change documentation
2026-04-23 chore: update documentation
2026-04-23 chore: minor changes to docs
2026-04-23 feat: gnuradio bugfix
2026-04-25 Deploy to github pages with github actions
2026-04-25 Add firmware to CI
2026-04-25 Pull tinyusb recursively
2026-04-25 MCO out as ADC CLK
2026-04-25 Variable declaration cleanup
2026-04-25 more debug for bitslip
2026-04-25 remove dac printout
2026-04-25 cleanup main.c
2026-04-25 Correct bitslip detection
2026-04-25 Make detection happen quicker
2026-04-25 Correct bitslip 'endianness'
2026-04-25 Correct URL
2026-04-25 feat: favicon logo change
2026-04-25 Encoder code
2026-04-25 use atan2 for fm demod
2026-04-25 FM DMA + works completely
2026-04-25 Swap to correct endianness
2026-04-25 Enable LM4809
2026-04-25 Colour schematics
2026-04-25 screen works
2026-04-25 Correct rotation
2026-04-25 FFT UI code
2026-04-25 chore: update readme
2026-04-26 Full width FFT
2026-04-26 reorg display code
2026-04-26 default enable FM out
2026-04-26 Code cleanup
2026-04-26 Filename cleanup
2026-04-26 Correct scroll
2026-04-26 Print frequency
2026-04-26 cmake cleanup
2026-04-26 dac fix
2026-04-26 gain control
2026-04-26 Faster bitslip stabilization
2026-04-26 display touch driver
2026-04-26 Optimize flash/ram usage
2026-04-27 Add volume and gain control to UI
2026-04-27 Increase SPI speed
2026-04-27 Init screen
2026-04-27 Reduce delays
2026-04-27 Add touch controller driver
2026-04-27 Optimise fft
2026-04-27 Add overclock
2026-04-27 Optimise fm demod
2026-04-27 Upgrade tinyusb
2026-04-27 FFT and I2S instruction level optimisation
2026-04-27 Better coefficients for polynomial approx
2026-04-27 Misc fixes
2026-04-27 Remove overclock
2026-04-28 fix: update webui link
2026-04-28 NBFM demod
2026-04-28 Refactor and optimise NBFM mode
2026-04-28 Reorder i2c init
2026-04-28 Push to usb audio
2026-04-28 Remove a copy from the audio out path
2026-04-28 more filtering and faster code
2026-05-02 Reduce CPU usage
2026-05-02 Add ADC voltage sampling
2026-05-02 More optimisation
2026-05-02 Optimised atan2
2026-05-03 Remove alt clock
2026-05-03 Refactor
2026-05-03 Add timer utilities
2026-05-04 Enable brown-out detection
2026-05-04 Increase PCLK1
2026-05-04 SDCard SDIO works
2026-05-04 Reading sd card works
2026-05-04 4bit SD works
2026-05-04 SD Card status printing
2026-05-04 Cleanup SD card path
2026-05-05 feat: basic splash screen
2026-05-05 feat: updated splash screen
2026-05-05 Clock setting refactoring
2026-05-06 Change linker script to reflect v305
2026-05-06 RAM optimisation
2026-05-07 Upgrade peripheral library to v3.0
2026-05-07 More watchdog
2026-05-07 RAM adjustments
2026-05-07 Make linker RAM report make sense
2026-05-14 tlv320 calibration parameters
2026-05-14 IQ calibration
2026-05-14 IQ calibration fixes
2026-05-14 IQ calibration polishing up
2026-05-14 IQ calibration UI fix
2026-05-14 Increase gain calibration range
2026-05-14 Better bitslip detection
2026-05-14 Improved si5351 tuning
2026-05-14 Faster init calibration
2026-05-15 feat: basic splash screen display
2026-05-15 feat: splash screen stuff
2026-05-15 feat:splash
2026-05-15 feat: landscape init
2026-05-15 feat: fm audio waveform visualisation on splash screen
2026-05-15 feat: attempt at splash screen optimisations
2026-05-15 chore: fps change
2026-05-16 chore: CMakeLists add size executable and depend on ld file
2026-05-16 chore: remove unused code
2026-05-16 feat: display speedup
2026-05-16 chore: more c++ simplification
2026-05-16 Add AGENTS.md
2026-05-16 chore: C23 ui.c
2026-05-16 feat: ui speedup
2026-05-16 feat: ui stack usage reduce
2026-05-16 chore: ui fft phases split
2026-05-16 feat: change default freq
2026-05-16 feat: spectrogram display
2026-05-16 feat: ui refactor
2026-05-16 feat: usb fix
2026-05-16 feat: optimise for production firmware
2026-05-16 feat: tinyusb+display stack ram savings
2026-05-16 feat: dac adjust for better audio buffering
2026-05-16 chore: tinyusb optimisations didn't work
2026-05-25 feat: remove double path to save flash space
2026-05-25 feat: AM demod
2026-05-25 feat: enable watchdog
2026-05-25 feat: USB/LSB modes
2026-05-25 feat: st7789 small packet optimisation
2026-05-26 chore: Update TinyUSB
2026-05-28 feat: Detect v1 board and route clock accordingly
2026-05-28 feat: bitslip reset way faster now
2026-05-28 chore: widen i2s correct window
2026-06-02 chore: i2s gpio cleanup
2026-06-02 feat: much faster and reliable bitslip
2026-06-02 feat: RNG driver
2026-06-02 feat: rng waiting for even faster i2s sync
2026-06-02 feat: ultra-fast sync
2026-06-08 feat: add support for low frequencies for si5351
2026-06-08 feat: wire up ui for new lower frequency
2026-06-08 feat: fix low freq latency
2026-06-08 chore: fix low freq edge clip
2026-06-08 feat: better low freq setting
2026-06-08 feat: even better low freq setting
2026-06-08 fix: low freq fix
2026-06-08 feat: more accurate low freq
2026-06-18 chore: hardware cicd test
2026-06-18 Add KiBot hardware CI configs
2026-06-18 Deploy hardware pages after failed checks
2026-06-18 Run DRC after ERC failures
2026-06-18 Update README with PCB Files viewer link
    Add link to Board PCB Files viewer in README
2026-06-18 Use VRML viewer for hardware 3D models
2026-06-21 Enhance README with additional images
    Added additional images to the README for better visualization.
